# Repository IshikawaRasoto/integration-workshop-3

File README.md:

# Melody - Team #6

This repository contains all the development of project Melody for the course of Integration Workshop 3 in UTFPR-CT.

## Links 🔗

- [Project Overview](Melody.md) 🎵
- [Blog](Blog.md) :pencil2:
- [Schedule](https://docs.google.com/spreadsheets/d/16BKpbmt_EArwLnEZPB5oZgRN8s5iP5gV15BQ9Iq-7wM/edit?usp=sharing) :calendar:
- [Requirements](https://docs.google.com/spreadsheets/d/1uYC0gMrYfBv8li1KcnDvk5HJS1G1zU4XR2CenMT3GNY/edit?usp=sharing) ✔️
- [Risk Plans](https://docs.google.com/document/d/1Hm508SiW-laHHYEpOHIg4PhOxUlGecafFV3NObWFzSE/edit?usp=sharing)

## Members

- Rafael Rasoto 

- Nicolas Riuichi Oda 

- Augusto Rosa  

- Bruno Zenatti  

- Fernando Caetano  

- Rogério Slabiski Melo

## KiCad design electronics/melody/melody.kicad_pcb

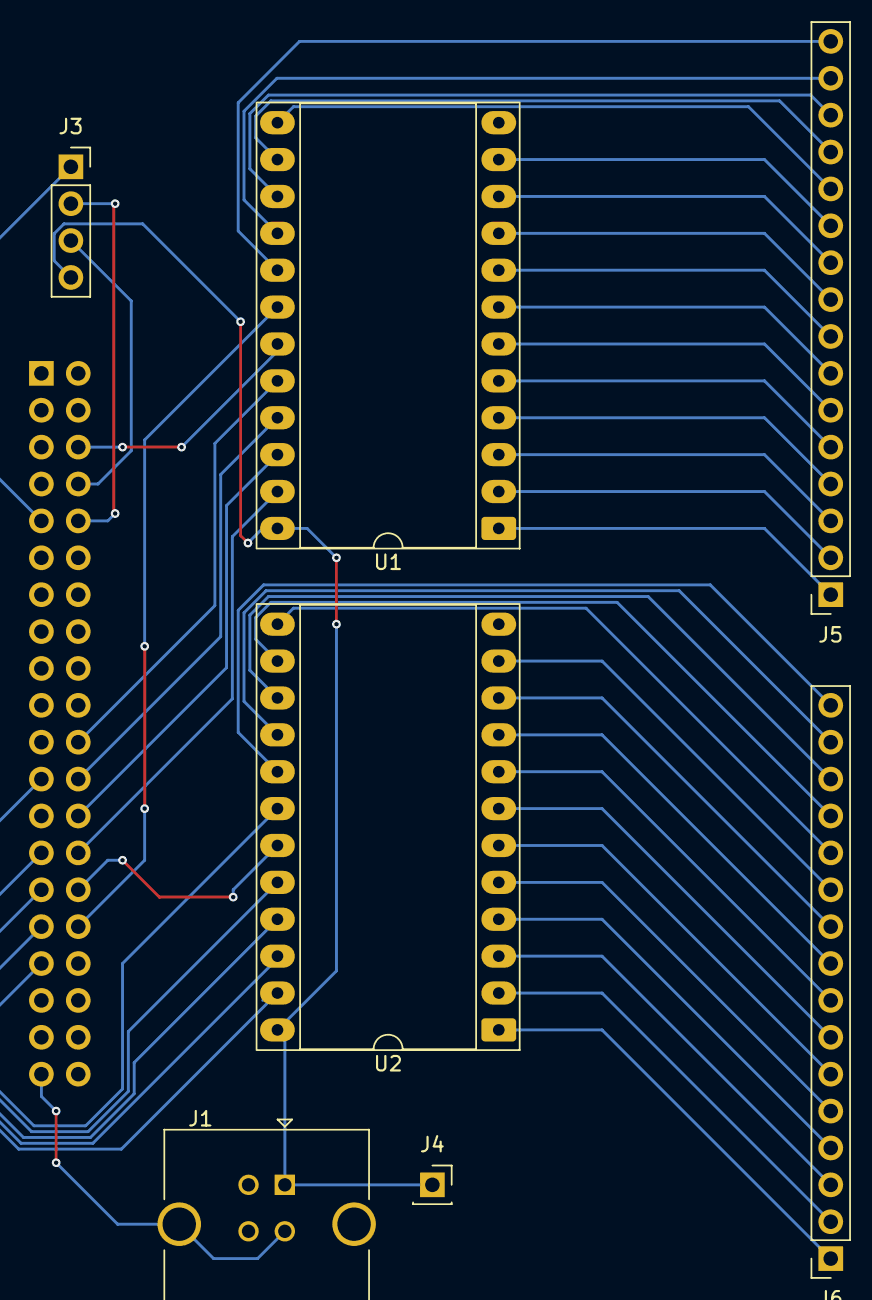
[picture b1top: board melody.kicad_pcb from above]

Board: 2 copper layers, 8 parts (1 on the bottom side), 46 nets.

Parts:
J1: USB_B; USB_B_TE_5787834_Vertical
J2: Raspberry_Pi_4; PinSocket_2x20_P2.54mm_Vertical
J3: Conn_01x04_Pin; PinSocket_1x04_P2.54mm_Vertical
J4: Conn_01x01_Pin; PinSocket_1x01_P2.54mm_Vertical
J5, J6: Conn_01x16_Pin; PinSocket_1x16_P2.54mm_Vertical
U1, U2: 74154; DIP-24_W15.24mm_Socket_LongPads

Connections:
/5V_OTHERS: J1.1 (VBUS), J3.4, J4.1, U1.24 (VCC), U2.24 (VCC)
/G0: J2.28 (ID_SC_I2C0/GPIO01), U1.23 (A0)
/G1: J2.26 (~CE1_SPI0/GPIO07), U1.22 (A1)
/G2: J2.24 (~CE0_SPI0/GPIO08), U1.21 (A2)
/G3: J2.22 (GPIO25/SDIO_DAT1), U1.20 (A3)
/GREEN_01: J5.1, U1.1 (~S0)
/GREEN_02: J5.2, U1.2 (~S1)
/GREEN_03: J5.3, U1.3 (~S2)
/GREEN_04: J5.4, U1.4 (~S3)
/GREEN_05: J5.5, U1.5 (~S4)
/GREEN_06: J5.6, U1.6 (~S5)
/GREEN_07: J5.7, U1.7 (~S6)
/GREEN_08: J5.8, U1.8 (~S7)
/GREEN_09: J5.9, U1.9 (~S8)
/GREEN_10: J5.10, U1.10 (~S9)
/GREEN_11: J5.11, U1.11 (~S10)
/GREEN_12: J5.12, U1.13 (~S11)
/GREEN_13: J5.13, U1.14 (~S12)
/GREEN_14: J5.14, U1.15 (~S13)
/GREEN_15: J5.15, U1.16 (~S14)
/GREEN_16: J5.16, U1.17 (~S15)
/MELODY_RX: J2.10 (GPIO15/UART_RXD), J3.2
/MELODY_TX: J2.8 (GPIO14/UART_TXD), J3.3
/PWM_GREEN: J2.32 (GPIO12/PWM0), U1.18 (~E0)
/PWM_RED: J2.33 (GPIO13/PWM1), U2.18 (~E0)
/R0: J2.23 (SCLK_SPI0/GPIO11), U2.23 (A0)
/R1: J2.27 (ID_SD_I2C0/GPIO00), U2.22 (A1)
/R2: J2.29 (GPCLK1/GPIO05), U2.21 (A2)
/R3: J2.31 (GPCLK2/GPIO06), U2.20 (A3)
/RED_01: J6.1, U2.1 (~S0)
/RED_02: J6.2, U2.2 (~S1)
/RED_03: J6.3, U2.3 (~S2)
/RED_04: J6.4, U2.4 (~S3)
/RED_05: J6.5, U2.5 (~S4)
/RED_06: J6.6, U2.6 (~S5)
/RED_07: J6.7, U2.7 (~S6)
/RED_08: J6.8, U2.8 (~S7)
/RED_09: J6.9, U2.9 (~S8)
/RED_10: J6.10, U2.10 (~S9)
/RED_11: J6.11, U2.11 (~S10)
/RED_12: J6.12, U2.13 (~S11)
/RED_13: J6.13, U2.14 (~S12)
/RED_14: J6.14, U2.15 (~S13)
/RED_15: J6.15, U2.16 (~S14)
/RED_16: J6.16, U2.17 (~S15)
GND: J1.4 (GND), J1.5 (Shield), J2.6 (GND), J2.9 (GND), J2.14 (GND), J2.20 (GND), J2.25 (GND), J2.30 (GND), J2.34 (GND), J2.39 (GND), J3.1, U1.12 (GND), U1.19 (~E1), U2.12 (GND), U2.19 (~E1)

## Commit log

2025-04-02 :memo: Update ReadME
2025-04-02 :memo: Create Blog.md
2025-04-02 :memo: Create Schedule.md
2025-04-02 :memo: Update README.md
2025-04-02 :memo: Update Blog.md, pending video
2025-04-03 :memo: Update Blog.md
2025-04-09 :memo: Create Melody.md
2025-04-09 :memo: Update Blog.md, pending this week's video
2025-04-10 :memo: Update Melody.md
2025-04-10 :memo: Create BajaValidation.md
2025-04-10 :memo: Update Blog.md Second linkage
2025-04-10 📝 Update Melody.md
2025-04-10 :memo: Update Melody.md - Professor Ott paragraph
2025-04-10 :memo: Update BajaValidation.md
2025-04-10 :memo: Update Melody.md - BOM
2025-04-10 :memo: Update BajaValidation.md - name update
2025-04-17 Add development environment requirements
2025-04-17 Update Requirements
2025-04-17 Swap RF19 and NFR04
2025-04-17 Add components for the accessibility module
2025-04-17 Update link to Schedule in Blog
2025-04-17 Possible Solutions added
2025-04-17 Add accessibility requirements
2025-04-17 Update links in README
2025-04-17 Update docs
2025-04-17 Deleted schedule.md
2025-04-17 :memo"Update Blog.md
2025-04-24 Rename RiskID4.pdf to ZXC
2025-04-24 Create test
2025-04-24 add probability explanation to risk 3
2025-04-24 Atualizar o Budget.md
2025-04-24 Atualizar o Blog.md
2025-04-24 Refactor Requirements.md
2025-04-26 updated requirements
2025-04-28 Removed obsolete risk plans
2025-04-28 Update Requirements and Schedule links
2025-04-28 Correction of Project Review link
2025-04-28 Update Rick analysis link
2025-04-28 added some simple risks
2025-04-29 added table to risk analysis
2025-05-02 Mechanical Design video
2025-05-02 link to budget doc updated
2025-05-09 add electronics
2025-05-13 added web interface
2025-05-13 adjusting images folder
2025-05-13 added common style
2025-05-14 change IC 74->40 + shared power supply for processors + PCB
2025-05-14 redirecting working and beginning of backend
2025-05-14 removec pycache
2025-05-14 communication front-back almost done, missing page, missing improvements
2025-05-14 added TODOs, missing testing backend->front
2025-05-14 fixed a detail
2025-05-16 added requirements
2025-05-16 explicando como rodar
2025-05-17 accessbility mode and same page for all clients
2025-05-17 resto em portugues
2025-05-17 structured files
2025-05-18 Melody schematic update
2025-05-18 structured modes, created main.py
2025-05-18 working mode redirecting
2025-05-18 adjusted details from tempo
2025-05-18 added mock of notes
2025-05-18 creation mode logic finished, missing playing and detection only
2025-05-20 fixed async
2025-05-20 sketch of playing notes
2025-05-20 improved delay between notes sounds
2025-05-20 adjusted tempo
2025-05-21 playing half and whole notes as well
2025-05-21 started hear and identify logic
2025-05-21 added the note detection thread
2025-05-21 added hear note button, added custom note
2025-05-21 adicionada documentação
2025-05-22 fixed details
2025-05-28 Atualização esquemático eletrônico
2025-05-28 NoteParser class implemented
2025-05-28 testes pre apresentacao
2025-05-28 added the correct notes for the musics in utils.py
2025-05-30 merged note_detection
2025-05-30 passing img as parameter
2025-05-30 added debug mode
2025-05-30 returning array of notes,durations
2025-05-30 started buttons interruptions
2025-05-30 sound volume adjusts working
2025-05-30 presentation code
2025-05-31 gpio for rasp
2025-05-31 detection thread salvando fotos
2025-05-31 Implemented Melodies
2025-05-31 button updating web
2025-05-31 detection thread
2025-05-31 buttons instances
2025-05-31 buttons gpio
2025-05-31 adjust to mode manager
2025-05-31 without comment
2025-05-31 comment
2025-05-31 volume adjust to 5 -5
2025-05-31 tempo commit
2025-05-31 calibration test
2025-05-31 calib colors
2025-05-31 working with fixed calibration
2025-05-31 working colors
2025-05-31 limitando buffer de video pra 1 frame
2025-05-31 updated interface com notas e melodias
2025-06-02 removed trash
2025-06-02 added duration to page
2025-06-02 removed Ovelha Preta and updating duration
2025-06-02 fixed webpage details
2025-06-02 identify mode implemented
2025-06-03 implemented hear mode
2025-06-03 accesbility on creation
2025-06-08 leds and buttons integrated
2025-06-08 change video
2025-06-08 add logo
2025-06-08 fixed image
2025-06-08 return None note when multiple notes detected per row
2025-06-08 added esp32 firmware
2025-06-08 fixed leds map
2025-06-09 detect only one note adjust colors
2025-06-09 debug game modes
2025-06-09 gamified modes finished
2025-06-11 fixed old note
2025-06-11 quick fix
2025-06-11 Atualizar o hardware.py
2025-06-12 add led module schematics
